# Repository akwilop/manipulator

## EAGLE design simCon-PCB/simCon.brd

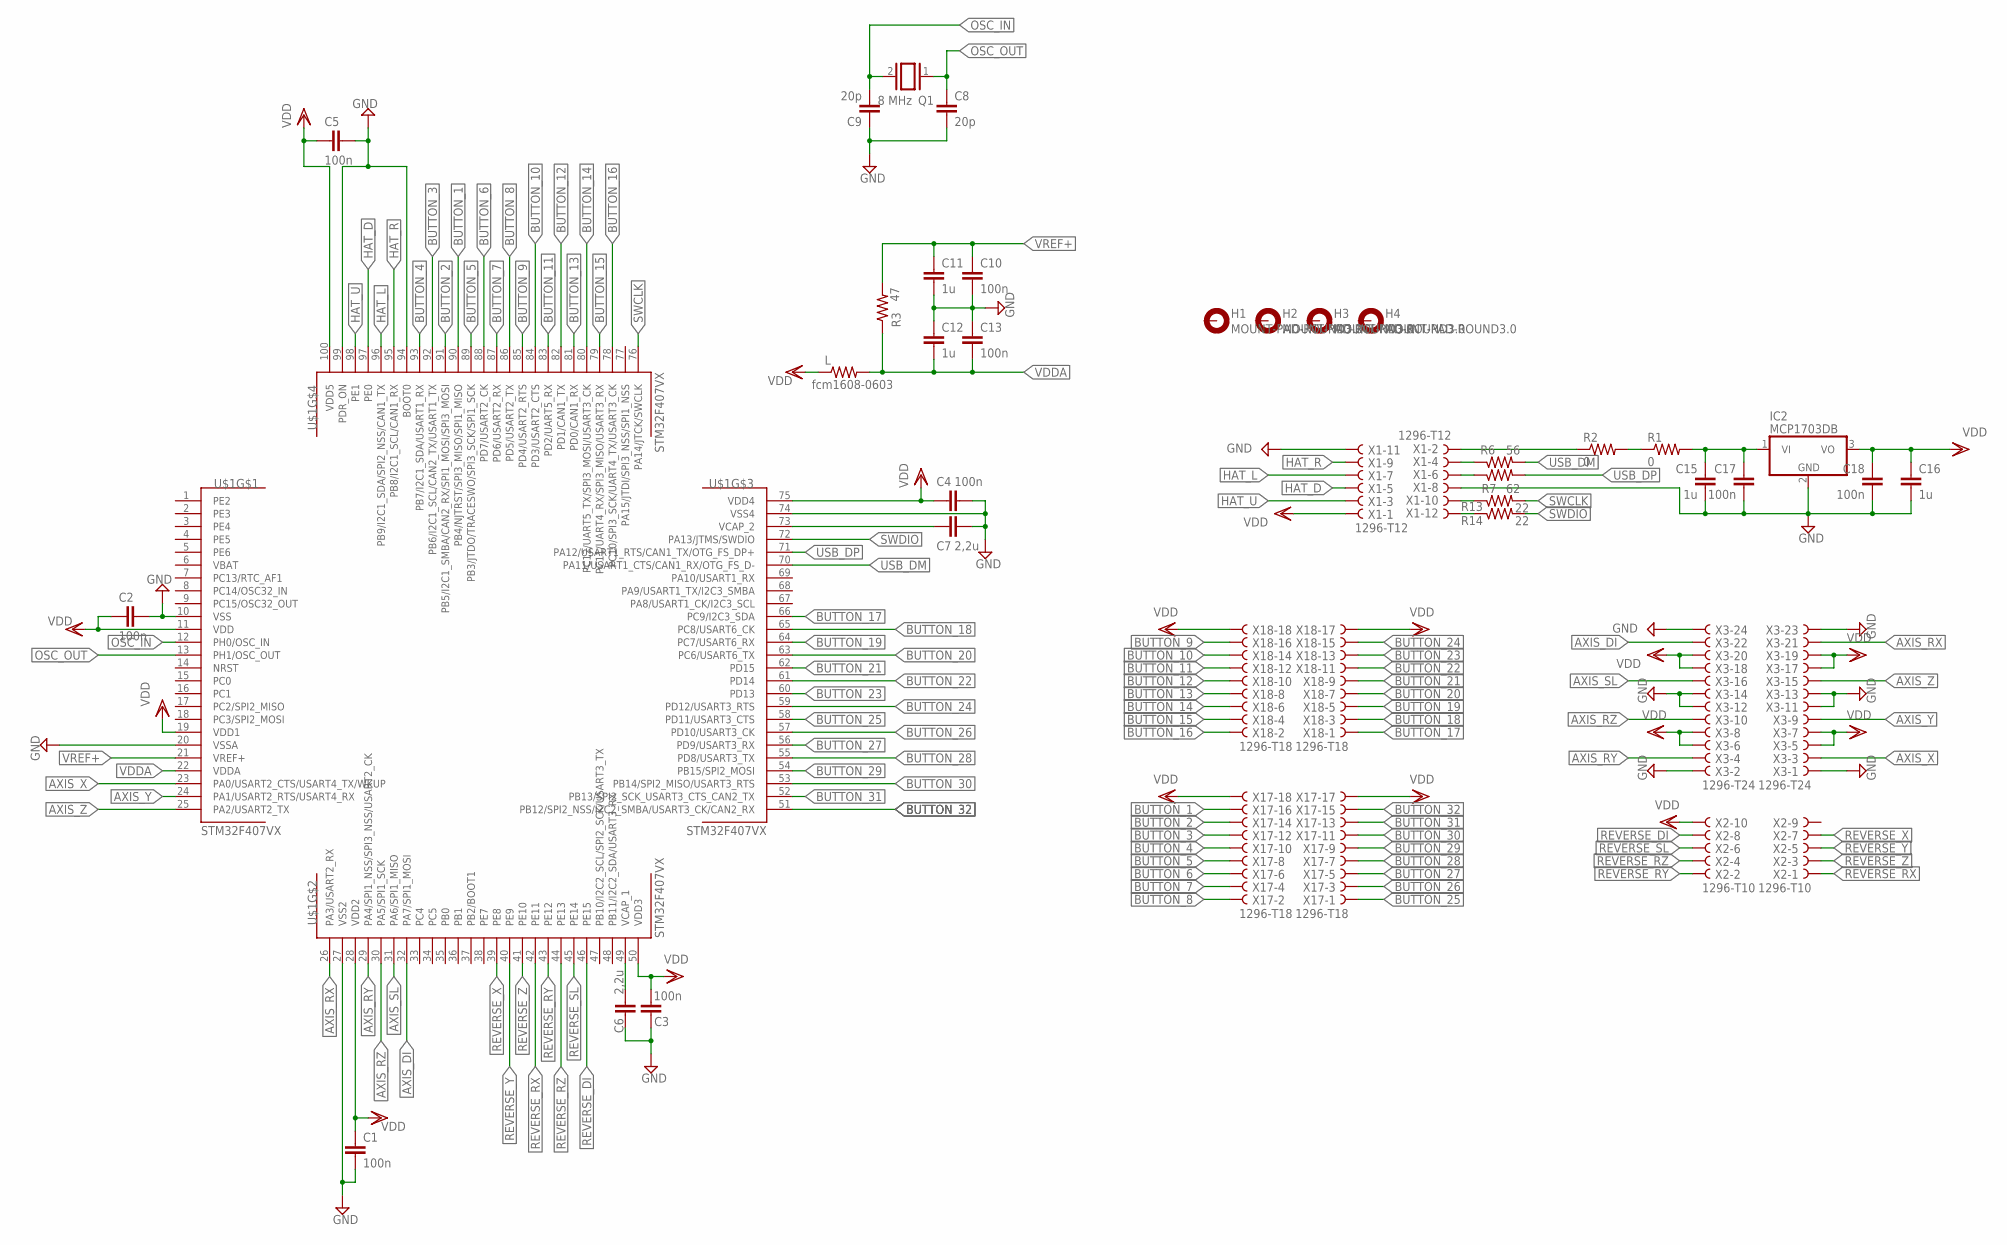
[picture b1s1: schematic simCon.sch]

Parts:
C1, C2, C3, C4, C5, C10, C13, C17, C18: 100n; C0805K
C6, C7: 2,2u; C0805K
C8, C9: 20p; C0805K
C11, C12, C15, C16: 1u; C0805K
H1, H2, H3, H4: MOUNT-PAD-ROUND3.0; 3,0-PAD
IC2: MCP1703DB; SOT223
L: fcm1608-0603; M0805
Q1: 8 MHz; QS
R1, R2: 0; R1206
R3: 47; M0805
R6: 56; M0805
R7: 62; M0805
R13, R14: 22; M0805
U$1: STM32F407VX; LQFP100
X1: 1296-T12; 1296-12
X2: 1296-T10; 1296-10
X3: 1296-T24; 1296-24
X17, X18: 1296-T18; 1296-18

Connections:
AXIS_DI: U$1.32 (PA7/SPI1_MOSI), X3.22
AXIS_RX: U$1.26 (PA3/USART2_RX), X3.21
AXIS_RY: U$1.29 (PA4/SPI1_NSS/SPI3_NSS/USART2_CK), X3.4
AXIS_RZ: U$1.30 (PA5/SPI1_SCK), X3.10
AXIS_SL: U$1.31 (PA6/SPI1_MISO), X3.16
AXIS_X: U$1.23 (PA0/USART2_CTS/USART4_TX/WKUP), X3.3
AXIS_Y: U$1.24 (PA1/USART2_RTS/USART4_RX), X3.9
AXIS_Z: U$1.25 (PA2/USART2_TX), X3.15
BUTTON_1: U$1.90 (PB4/NJTRST/SPI3_MISO/SPI1_MISO), X17.16
BUTTON_2: U$1.91 (PB5/I2C1_SMBA/CAN2_RX/SPI1_MOSI/SPI3_MO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), X17.14
BUTTON_3: U$1.92 (PB6/I2C1_SCL/CAN2_TX/USART1_TX), X17.12
BUTTON_4: U$1.93 (PB7/I2C1_SDA/USART1_RX), X17.10
BUTTON_5: U$1.89 (PB3/JTDO/TRACESWO/SPI3_SCK/SPI1_SCK), X17.8
BUTTON_6: U$1.88 (PD7/USART2_CK), X17.6
BUTTON_7: U$1.87 (PD6/USART2_RX), X17.4
BUTTON_8: U$1.86 (PD5/USART2_TX), X17.2
BUTTON_9: U$1.85 (PD4/USART2_RTS), X18.16
BUTTON_10: U$1.84 (PD3/USART2_CTS), X18.14
BUTTON_11: U$1.83 (PD2/UART5_RX), X18.12
BUTTON_12: U$1.82 (PD1/CAN1_TX), X18.10
BUTTON_13: U$1.81 (PD0/CAN1_RX), X18.8
BUTTON_14: U$1.80 (PC12/UART5_TX/SPI3_MOSI/USART3_CK), X18.6
BUTTON_15: U$1.79 (PC11/UART4_RX/SPI3_MISO/USART3_RX), X18.4
BUTTON_16: U$1.78 (PC10/SPI3_SCK/UART4_TX/USART3_CK), X18.2
BUTTON_17: U$1.66 (PC9/I2C3_SDA), X18.1
BUTTON_18: U$1.65 (PC8/USART6_CK), X18.3
BUTTON_19: U$1.64 (PC7/USART6_RX), X18.5
BUTTON_20: U$1.63 (PC6/USART6_TX), X18.7
BUTTON_21: U$1.62 (PD15), X18.9
BUTTON_22: U$1.61 (PD14), X18.11
BUTTON_23: U$1.60 (PD13), X18.13
BUTTON_24: U$1.59 (PD12/USART3_RTS), X18.15
BUTTON_25: U$1.58 (PD11/USART3_CTS), X17.1
BUTTON_26: U$1.57 (PD10/USART3_CK), X17.3
BUTTON_27: U$1.56 (PD9/USART3_RX), X17.5
BUTTON_28: U$1.55 (PD8/USART3_TX), X17.7
BUTTON_29: U$1.54 (PB15/SPI2_MOSI), X17.9
BUTTON_30: U$1.53 (PB14/SPI2_MISO/USART3_RTS), X17.11
BUTTON_31: U$1.52 (PB13/SPI2_SCK_USART3_CTS_CAN2_TX), X17.13
BUTTON_32: U$1.51 (PB12/SPI2_NSS/I2C2_SMBA/USART3_CK/CAN2_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), X17.15
GND: C1.2, C2.1, C3.1, C4.1, C5.1, C6.1, C7.1, C8.2, C9.1, C10.2, C11.2, C12.1, C13.1, C15.2, C16.2, C17.2, C18.2, IC2.2 (GND), U$1.10 (VSS), U$1.20 (VSSA), U$1.27 (VSS2), U$1.74 (VSS4), U$1.94 (BOOT0), U$1.99 (PDR_ON), X1.8, X1.11, X3.1, X3.2, X3.11, X3.12, X3.13, X3.14, X3.23, X3.24
HAT_D: U$1.97 (PE0), X1.5
HAT_L: U$1.96 (PB9/I2C1_SDA/SPI2_NSS/CAN1_TX), X1.7
HAT_R: U$1.95 (PB8/I2C1_SCL/CAN1_RX), X1.9
HAT_U: U$1.98 (PE1), X1.3
unnamed: C7.2, U$1.73 (VCAP_2)
unnamed: C6.2, U$1.49 (VCAP_1)
unnamed: R6.1, X1.4
unnamed: R7.1, X1.6
unnamed: R14.1, X1.12
unnamed: R13.1, X1.10
unnamed: R2.1, X1.2
unnamed: R1.1, R2.2
unnamed: C15.1, C17.1, IC2.1 (VI), R1.2
OSC_IN: C9.2, Q1.2, U$1.12 (PH0/OSC_IN)
OSC_OUT: C8.1, Q1.1, U$1.13 (PH1/OSC_OUT)
REVERSE_DI: U$1.46 (PE15), X2.8
REVERSE_RX: U$1.42 (PE11), X2.1
REVERSE_RY: U$1.43 (PE12), X2.2
REVERSE_RZ: U$1.44 (PE13), X2.4
REVERSE_SL: U$1.45 (PE14), X2.6
REVERSE_X: U$1.39 (PE8), X2.7
REVERSE_Y: U$1.40 (PE9), X2.5
REVERSE_Z: U$1.41 (PE10), X2.3
SWCLK: R13.2, U$1.76 (PA14/JTCK/SWCLK)
SWDIO: R14.2, U$1.72 (PA13/JTMS/SWDIO)
USB_DM: R6.2, U$1.70 (PA11/USART1_CTS/CAN1_RX/OTG_FS_D-)
USB_DP: R7.2, U$1.71 (PA12/USART1_RTS/CAN1_TX/OTG_FS_DP+)
VDD: C1.1, C2.2, C3.2, C4.2, C5.2, C16.1, C18.1, IC2.3 (VO), L.1, U$1.11 (VDD), U$1.19 (VDD1), U$1.28 (VDD2), U$1.50 (VDD3), U$1.75 (VDD4), U$1.100 (VDD5), X1.1, X2.10, X3.5, X3.6, X3.7, X3.8, X3.17, X3.18, X3.19, X3.20, X17.17, X17.18, X18.17, X18.18
VDDA: C12.2, C13.2, L.2, R3.1, U$1.22 (VDDA)
VREF+: C10.1, C11.1, R3.2, U$1.21 (VREF+)

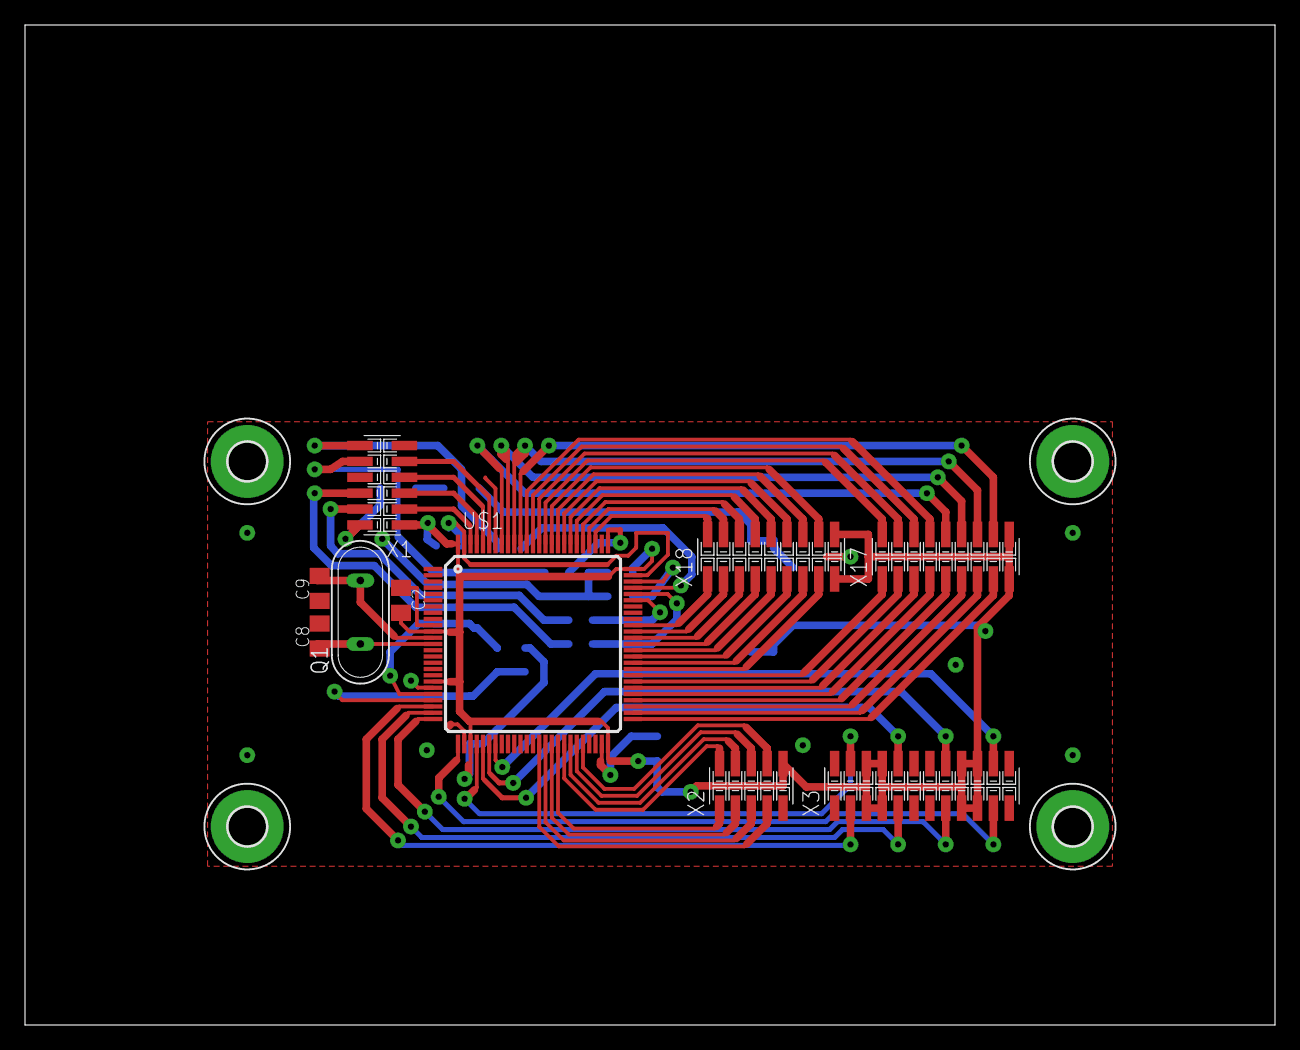
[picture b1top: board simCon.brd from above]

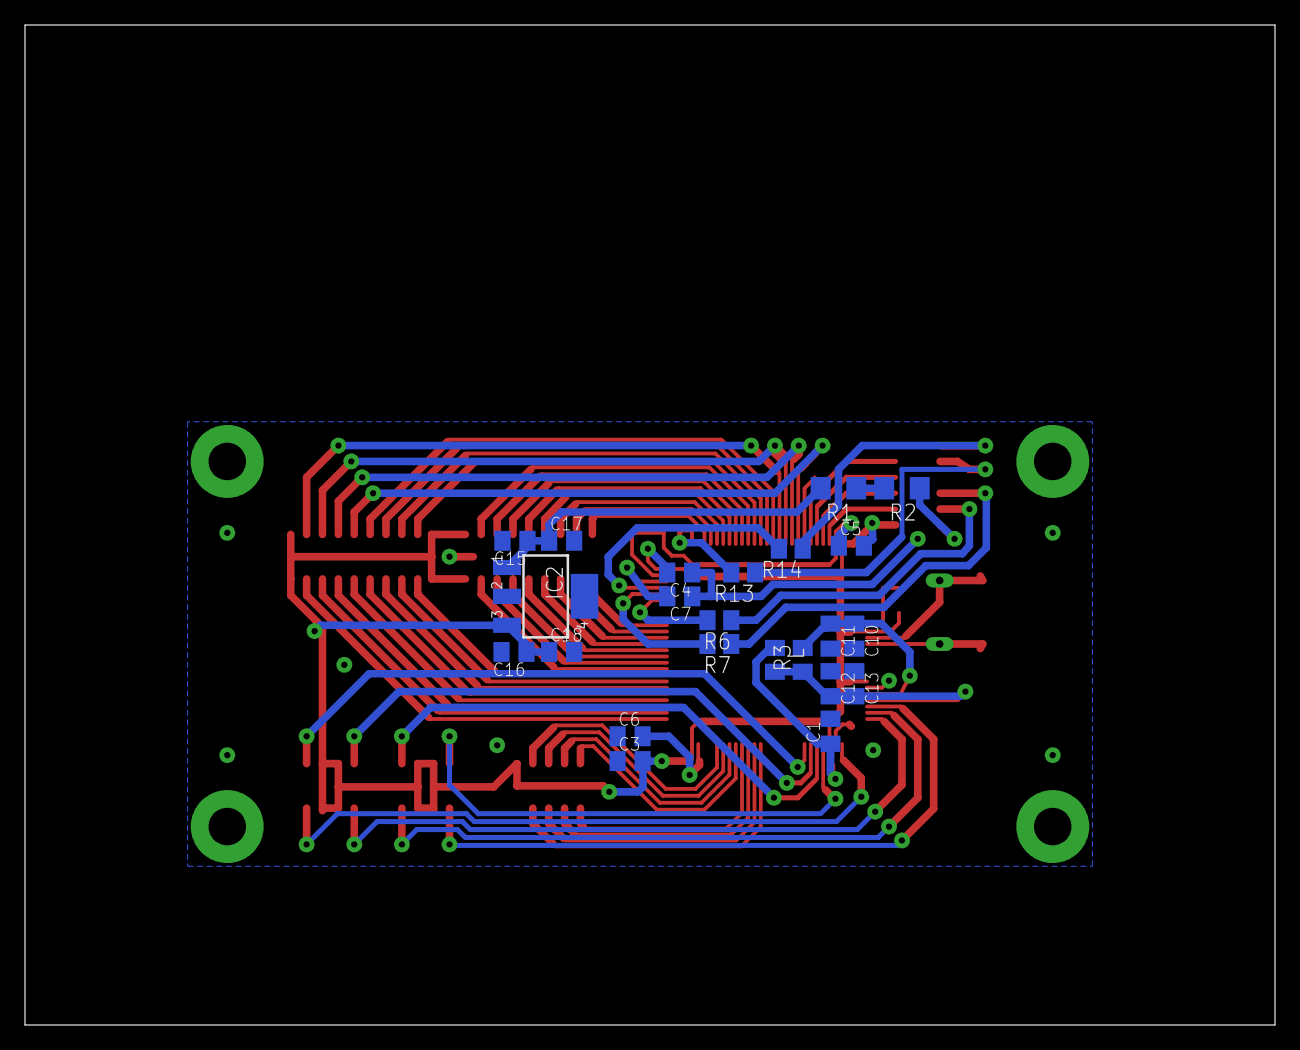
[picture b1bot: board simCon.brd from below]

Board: 2 copper layers, 100.0 x 80.0 mm, 37 parts (23 on the bottom side), 71 nets.

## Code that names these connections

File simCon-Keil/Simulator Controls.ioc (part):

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Mcu.Name=STM32F407V(E-G)Tx
Mcu.Package=LQFP100
Mcu.UserName=STM32F407VGTx
PA0-WKUP.GPIOParameters=GPIO_Label
PA0-WKUP.GPIO_Label=AXIS_X
PA0-WKUP.Signal=ADCx_IN0
PA1.GPIOParameters=GPIO_Label
PA1.GPIO_Label=AXIS_Y
PA1.Signal=ADCx_IN1
PA10.GPIOParameters=GPIO_PuPd,GPIO_Label,GPIO_Mode
PA10.GPIO_Label=BUTTON_25
PA10.GPIO_Mode=GPIO_MODE_INPUT
PA10.GPIO_PuPd=GPIO_PULLDOWN
PA10.Signal=GPIO_Input
PA11.GPIOParameters=GPIO_Label
PA11.GPIO_Label=USB_DM
PA11.Mode=Device_Only
PA11.Signal=USB_OTG_FS_DM
PA12.GPIOParameters=GPIO_Label
PA12.GPIO_Label=USB_DP
PA12.Mode=Device_Only
PA12.Signal=USB_OTG_FS_DP
PA13.GPIOParameters=GPIO_Label
PA13.GPIO_Label=SWDIO
PA13.Mode=Serial_Wire
PA13.Signal=SYS_JTMS-SWDIO
PA14.GPIOParameters=GPIO_Label
PA14.GPIO_Label=SWCLK
PA14.Mode=Serial_Wire
PA14.Signal=SYS_JTCK-SWCLK
PA2.GPIOParameters=GPIO_Label
PA2.GPIO_Label=AXIS_Z
PA2.Signal=ADCx_IN2
PA3.GPIOParameters=GPIO_Label
PA3.GPIO_Label=ROT_X
PA3.Signal=ADCx_IN3
PA4.GPIOParameters=GPIO_Label
PA4.GPIO_Label=ROT_Y
PA4.Signal=ADCx_IN4
PA5.GPIOParameters=GPIO_Label
PA5.GPIO_Label=ROT_Z
PA5.Signal=ADCx_IN5
PA6.GPIOParameters=GPIO_Label
PA6.GPIO_Label=SLIDER
PA6.Signal=ADCx_IN6
PA7.GPIOParameters=GPIO_Label
PA7.GPIO_Label=DIAL
PA7.Signal=ADCx_IN7
PA8.GPIOParameters=GPIO_PuPd,GPIO_Label,GPIO_Mode
PA8.GPIO_Label=BUTTON_23
PA8.GPIO_Mode=GPIO_MODE_INPUT
PA8.GPIO_PuPd=GPIO_PULLDOWN
PA8.Signal=GPIO_Input
PA9.GPIOParameters=GPIO_PuPd,GPIO_Label,GPIO_Mode
PA9.GPIO_Label=BUTTON_24
PA9.GPIO_Mode=GPIO_MODE_INPUT
PA9.GPIO_PuPd=GPIO_PULLDOWN
PA9.Signal=GPIO_Input
PB0.GPIOParameters=GPIO_Label
PB0.GPIO_Label=Y_FEED_PWM_1
PB0.Signal=S_TIM3_CH3
PB1.GPIOParameters=GPIO_Label
PB1.GPIO_Label=Y_FEED_PWM_2
PB1.Signal=S_TIM3_CH4
PB10.Mode=I2C
PB10.Signal=I2C2_SCL
PB11.Mode=I2C
PB11.Signal=I2C2_SDA
PB12.GPIOParameters=GPIO_PuPd,GPIO_Label,GPIO_Mode
PB12.GPIO_Label=BUTTON_13
PB12.GPIO_Mode=GPIO_MODE_INPUT
PB12.GPIO_PuPd=GPIO_PULLDOWN
PB12.Signal=GPIO_Input
PB13.GPIOParameters=GPIO_PuPd,GPIO_Label,GPIO_Mode
PB13.GPIO_Label=BUTTON_14
PB13.GPIO_Mode=GPIO_MODE_INPUT
PB13.GPIO_PuPd=GPIO_PULLDOWN
PB13.Signal=GPIO_Input
PB14.GPIOParameters=GPIO_PuPd,GPIO_Label,GPIO_Mode
PB14.GPIO_Label=BUTTON_15
PB14.GPIO_Mode=GPIO_MODE_INPUT
PB14.GPIO_PuPd=GPIO_PULLDOWN
PB14.Signal=GPIO_Input
PB15.GPIOParameters=GPIO_PuPd,GPIO_Label,GPIO_Mode
PB15.GPIO_Label=BUTTON_16
PB15.GPIO_Mode=GPIO_MODE_INPUT
PB15.GPIO_PuPd=GPIO_PULLDOWN
PB15.Signal=GPIO_Input
PB2.GPIOParameters=GPIO_PuPd,GPIO_Label,GPIO_Mode
PB2.GPIO_Label=BUTTON_3
PB2.GPIO_Mode=GPIO_MODE_INPUT
PB2.GPIO_PuPd=GPIO_PULLDOWN
PB2.Signal=GPIO_Input
PB3.Mode=Full_Duplex_Master
PB3.Signal=SPI1_SCK
PB4.Mode=Full_Duplex_Master
PB4.Signal=SPI1_MISO
PB5.Mode=Full_Duplex_Master
PB5.Signal=SPI1_MOSI
PB6.Mode=I2C
PB6.Signal=I2C1_SCL
PB7.Mode=I2C
PB7.Signal=I2C1_SDA
PB8.GPIOParameters=GPIO_PuPd,GPIO_Label,GPIO_Mode
PB8.GPIO_Label=SLIDER_FEED_EN
PB8.GPIO_Mode=GPIO_MODE_INPUT
PB8.GPIO_PuPd=GPIO_PULLDOWN
PB8.Signal=GPIO_Input
PB9.GPIOParameters=GPIO_PuPd,GPIO_Label,GPIO_Mode
PB9.GPIO_Label=Z_FEED_EN
PB9.GPIO_Mode=GPIO_MODE_INPUT
PB9.GPIO_PuPd=GPIO_PULLDOWN
PB9.Signal=GPIO_Input
PC10.Mode=Full_Duplex_Master
PC10.Signal=SPI3_SCK
PC11.Mode=Full_Duplex_Master
PC11.Signal=SPI3_MISO
PC12.Mode=Full_Duplex_Master
PC12.Signal=SPI3_MOSI
PC4.GPIOParameters=GPIO_PuPd,GPIO_Label,GPIO_Mode
PC4.GPIO_Label=BUTTON_1
PC4.GPIO_Mode=GPIO_MODE_INPUT
PC4.GPIO_PuPd=GPIO_PULLDOWN
PC4.Signal=GPIO_Input
PC5.GPIOParameters=GPIO_PuPd,GPIO_Label,GPIO_Mode
PC5.GPIO_Label=BUTTON_2
PC5.GPIO_Mode=GPIO_MODE_INPUT
PC5.GPIO_PuPd=GPIO_PULLDOWN
PC5.Signal=GPIO_Input
PC6.GPIOParameters=GPIO_Label
PC6.GPIO_Label=X_FEED_PWM_1
PC6.Signal=S_TIM3_CH1
PC7.GPIOParameters=GPIO_Label
PC7.GPIO_Label=X_FEED_PWM_2
PC7.Signal=S_TIM3_CH2
PC8.GPIOParameters=GPIO_PuPd,GPIO_Label,GPIO_Mode
PC8.GPIO_Label=BUTTON_21
PC8.GPIO_Mode=GPIO_MODE_INPUT
PC8.GPIO_PuPd=GPIO_PULLDOWN
PC8.Signal=GPIO_Input
PC9.GPIOParameters=GPIO_PuPd,GPIO_Label,GPIO_Mode
PC9.GPIO_Label=BUTTON_22
PC9.GPIO_Mode=GPIO_MODE_INPUT
PC9.GPIO_PuPd=GPIO_PULLDOWN
PC9.Signal=GPIO_Input
PD0.GPIOParameters=GPIO_PuPd,GPIO_Label,GPIO_Mode
PD0.GPIO_Label=BUTTON_26
PD0.GPIO_Mode=GPIO_MODE_INPUT
PD0.GPIO_PuPd=GPIO_PULLDOWN
PD0.Signal=GPIO_Input
PD1.GPIOParameters=GPIO_PuPd,GPIO_Label,GPIO_Mode
PD1.GPIO_Label=BUTTON_27
PD1.GPIO_Mode=GPIO_MODE_INPUT
PD1.GPIO_PuPd=GPIO_PULLDOWN
PD1.Signal=GPIO_Input
PD10.GPIOParameters=GPIO_PuPd,GPIO_Label,GPIO_Mode
PD10.GPIO_Label=BUTTON_19
PD10.GPIO_Mode=GPIO_MODE_INPUT
PD10.GPIO_PuPd=GPIO_PULLDOWN
PD10.Signal=GPIO_Input
PD11.GPIOParameters=GPIO_PuPd,GPIO_Label,GPIO_Mode
PD11.GPIO_Label=BUTTON_20
PD11.GPIO_Mode=GPIO_MODE_INPUT
PD11.GPIO_PuPd=GPIO_PULLDOWN
PD11.Signal=GPIO_Input
PD12.GPIOParameters=GPIO_Label
PD12.GPIO_Label=Z_FEED_PWM_1
PD12.Signal=S_TIM4_CH1
PD13.GPIOParameters=GPIO_Label
PD13.GPIO_Label=Z_FEED_PWM_2
PD13.Signal=S_TIM4_CH2
PD14.GPIOParameters=GPIO_Label
PD14.GPIO_Label=SLIDER_FEED_PWM_1
PD14.Signal=S_TIM4_CH3
PD15.GPIOParameters=GPIO_Label
PD15.GPIO_Label=SLIDER_FEED_PWM_2
PD15.Signal=S_TIM4_CH4
PD2.GPIOParameters=GPIO_PuPd,GPIO_Label,GPIO_Mode
PD2.GPIO_Label=BUTTON_28
PD2.GPIO_Mode=GPIO_MODE_INPUT
PD2.GPIO_PuPd=GPIO_PULLDOWN
PD2.Signal=GPIO_Input
PD3.GPIOParameters=GPIO_PuPd,GPIO_Label,GPIO_Mode
PD3.GPIO_Label=BUTTON_29
PD3.GPIO_Mode=GPIO_MODE_INPUT
PD3.GPIO_PuPd=GPIO_PULLDOWN
PD3.Signal=GPIO_Input
PD4.GPIOParameters=GPIO_PuPd,GPIO_Label,GPIO_Mode
PD4.GPIO_Label=BUTTON_30
PD4.GPIO_Mode=GPIO_MODE_INPUT
PD4.GPIO_PuPd=GPIO_PULLDOWN
PD4.Signal=GPIO_Input
PD5.GPIOParameters=GPIO_PuPd,GPIO_Label,GPIO_Mode
PD5.GPIO_Label=BUTTON_31
PD5.GPIO_Mode=GPIO_MODE_INPUT
PD5.GPIO_PuPd=GPIO_PULLDOWN
PD5.Signal=GPIO_Input
PD6.GPIOParameters=GPIO_PuPd,GPIO_Label,GPIO_Mode
PD6.GPIO_Label=BUTTON_32
PD6.GPIO_Mode=GPIO_MODE_INPUT
PD6.GPIO_PuPd=GPIO_PULLDOWN
PD6.Signal=GPIO_Input
PD8.GPIOParameters=GPIO_PuPd,GPIO_Label,GPIO_Mode
PD8.GPIO_Label=BUTTON_17
PD8.GPIO_Mode=GPIO_MODE_INPUT
PD8.GPIO_PuPd=GPIO_PULLDOWN
PD8.Signal=GPIO_Input
PD9.GPIOParameters=GPIO_PuPd,GPIO_Label,GPIO_Mode
PD9.GPIO_Label=BUTTON_18
PD9.GPIO_Mode=GPIO_MODE_INPUT
PD9.GPIO_PuPd=GPIO_PULLDOWN
PD9.Signal=GPIO_Input
PE0.GPIOParameters=GPIO_PuPd,GPIO_Label,GPIO_Mode
PE0.GPIO_Label=Y_FEED_EN
PE0.GPIO_Mode=GPIO_MODE_INPUT
PE0.GPIO_PuPd=GPIO_PULLDOWN
PE0.Signal=GPIO_Input
PE1.GPIOParameters=GPIO_PuPd,GPIO_Label,GPIO_Mode
PE1.GPIO_Label=X_FEED_EN
PE1.GPIO_Mode=GPIO_MODE_INPUT
PE1.GPIO_PuPd=GPIO_PULLDOWN
PE1.Signal=GPIO_Input
PE10.GPIOParameters=GPIO_PuPd,GPIO_Label,GPIO_Mode
PE10.GPIO_Label=BUTTON_7
PE10.GPIO_Mode=GPIO_MODE_INPUT
PE10.GPIO_PuPd=GPIO_PULLDOWN
PE10.Signal=GPIO_Input
PE11.GPIOParameters=GPIO_PuPd,GPIO_Label,GPIO_Mode
PE11.GPIO_Label=BUTTON_8
PE11.GPIO_Mode=GPIO_MODE_INPUT
PE11.GPIO_PuPd=GPIO_PULLDOWN
PE11.Signal=GPIO_Input
PE12.GPIOParameters=GPIO_PuPd,GPIO_Label,GPIO_Mode
PE12.GPIO_Label=BUTTON_9
PE12.GPIO_Mode=GPIO_MODE_INPUT
PE12.GPIO_PuPd=GPIO_PULLDOWN
PE12.Signal=GPIO_Input
PE13.GPIOParameters=GPIO_PuPd,GPIO_Label,GPIO_Mode
PE13.GPIO_Label=BUTTON_10
PE13.GPIO_Mode=GPIO_MODE_INPUT
PE13.GPIO_PuPd=GPIO_PULLDOWN
PE13.Signal=GPIO_Input
PE14.GPIOParameters=GPIO_PuPd,GPIO_Label,GPIO_Mode
PE14.GPIO_Label=BUTTON_11
PE14.GPIO_Mode=GPIO_MODE_INPUT
PE14.GPIO_PuPd=GPIO_PULLDOWN
PE14.Signal=GPIO_Input
PE15.GPIOParameters=GPIO_PuPd,GPIO_Label,GPIO_Mode
PE15.GPIO_Label=BUTTON_12
PE15.GPIO_Mode=GPIO_MODE_INPUT
PE15.GPIO_PuPd=GPIO_PULLDOWN
PE15.Signal=GPIO_Input
PE2.GPIOParameters=GPIO_PuPd,GPIO_Label,GPIO_Mode
PE2.GPIO_Label=HAT_U
PE2.GPIO_Mode=GPIO_MODE_INPUT
PE2.GPIO_PuPd=GPIO_PULLDOWN
PE2.Signal=GPIO_Input
PE3.GPIOParameters=GPIO_PuPd,GPIO_Label,GPIO_Mode
PE3.GPIO_Label=HAT_D
PE3.GPIO_Mode=GPIO_MODE_INPUT
PE3.GPIO_PuPd=GPIO_PULLDOWN
PE3.Signal=GPIO_Input
PE4.GPIOParameters=GPIO_PuPd,GPIO_Label,GPIO_Mode
PE4.GPIO_Label=HAT_R
PE4.GPIO_Mode=GPIO_MODE_INPUT
PE4.GPIO_PuPd=GPIO_PULLDOWN
PE4.Signal=GPIO_Input
PE5.GPIOParameters=GPIO_PuPd,GPIO_Label,GPIO_Mode
PE5.GPIO_Label=HAT_L
PE5.GPIO_Mode=GPIO_MODE_INPUT
PE5.GPIO_PuPd=GPIO_PULLDOWN
PE5.Signal=GPIO_Input
PE7.GPIOParameters=GPIO_PuPd,GPIO_Label,GPIO_Mode
PE7.GPIO_Label=BUTTON_4
PE7.GPIO_Mode=GPIO_MODE_INPUT
PE7.GPIO_PuPd=GPIO_PULLDOWN
PE7.Signal=GPIO_Input
PE8.GPIOParameters=GPIO_PuPd,GPIO_Label,GPIO_Mode
PE8.GPIO_Label=BUTTON_5
PE8.GPIO_Mode=GPIO_MODE_INPUT
PE8.GPIO_PuPd=GPIO_PULLDOWN
PE8.Signal=GPIO_Input
PE9.GPIOParameters=GPIO_PuPd,GPIO_Label,GPIO_Mode
PE9.GPIO_Label=BUTTON_6
PE9.GPIO_Mode=GPIO_MODE_INPUT
PE9.GPIO_PuPd=GPIO_PULLDOWN
PE9.Signal=GPIO_Input
PH0-OSC_IN.Mode=HSE-External-Oscillator
PH0-OSC_IN.Signal=RCC_OSC_IN
PH1-OSC_OUT.Mode=HSE-External-Oscillator
PH1-OSC_OUT.Signal=RCC_OSC_OUT
RCC.HSE_VALUE=8000000
RCC.SYSCLKFreq_VALUE=168000000
RCC.SYSCLKSource=RCC_SYSCLKSOURCE_PLLCLK
board=Simulator Controls

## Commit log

2017-04-26 :lollipop: Added .gitattributes
2017-04-26 Praca inżynierska
    Wielokanałowy manipulator symulatorowy z kalibracją wewnętrzną

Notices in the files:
parts and their libraries:
STM32F407Vx_LQFP100: Copyright 2012 by Ersan Günes, Quantitec, info@quantitec.de
